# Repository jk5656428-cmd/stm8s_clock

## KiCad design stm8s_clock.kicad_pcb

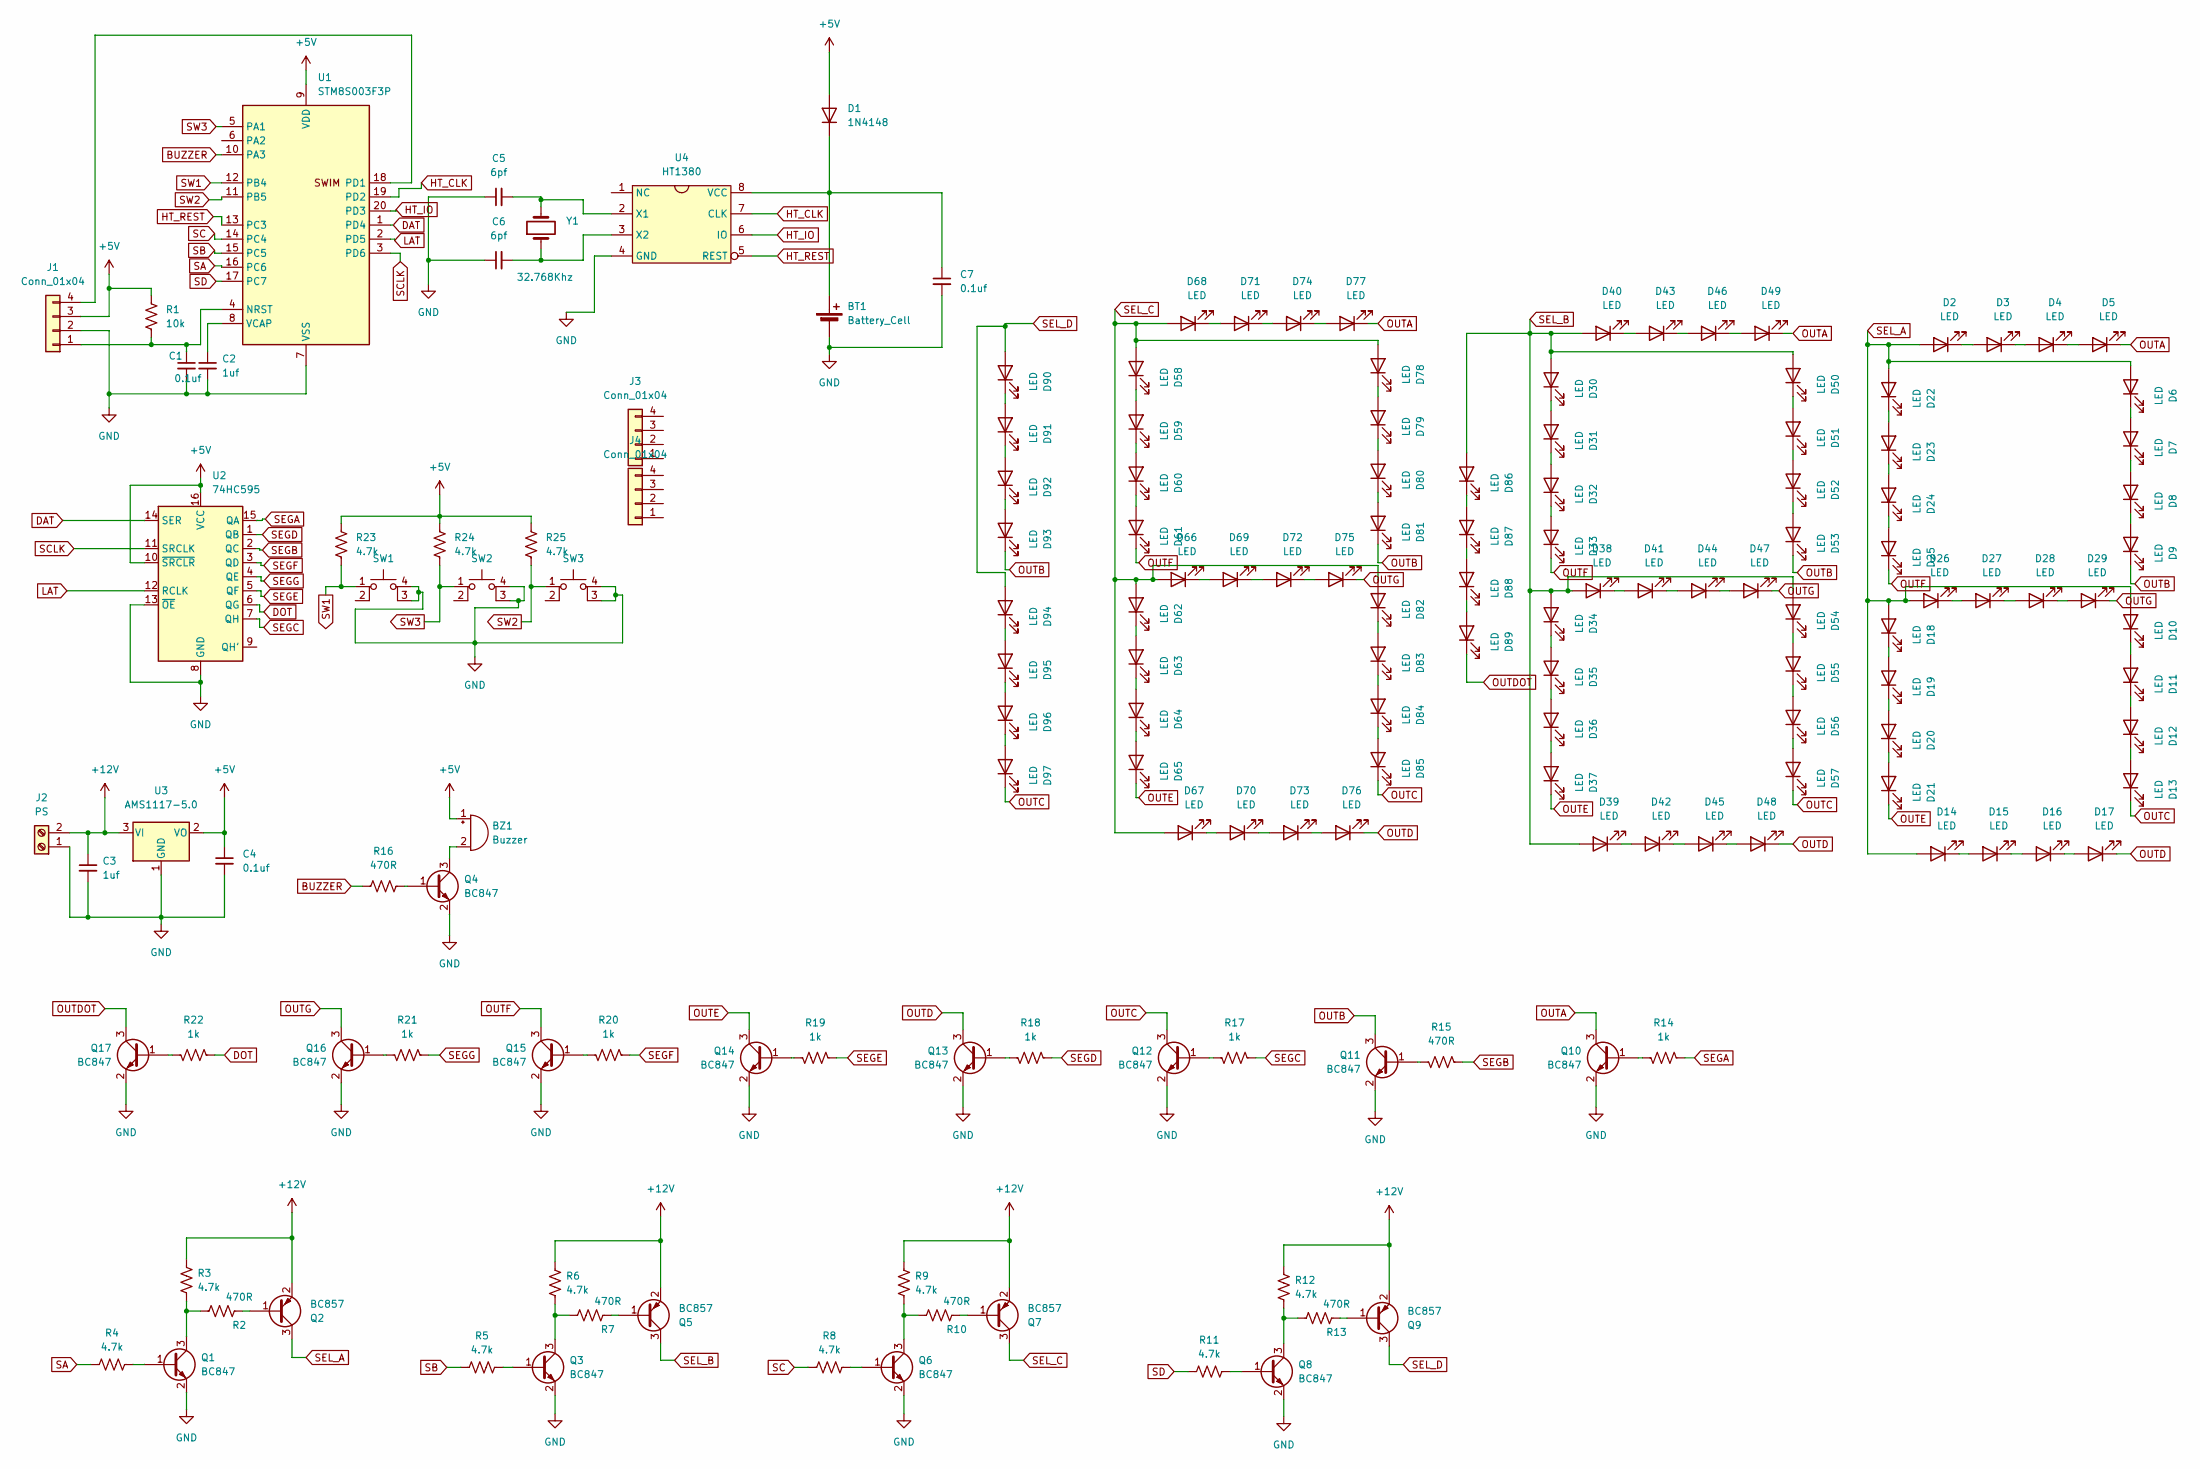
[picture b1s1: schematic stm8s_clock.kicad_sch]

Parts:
BT1: Battery_Cell
BZ1: Buzzer; Buzzer_12x9.5RM7.6
C1: 0.1uf; C_1206_3216Metric_Pad1.33x1.80mm_HandSolder
C2: 1uf; C_0805_2012Metric_Pad1.18x1.45mm_HandSolder
C3: 1uf; C_1206_3216Metric
C4, C7: 0.1uf; C_1206_3216Metric
C5, C6: 6pf; C_Disc_D5.0mm_W2.5mm_P5.00mm
D1: 1N4148; D_DO-35_SOD27_P7.62mm_Horizontal
D2, D3, D4, D5, D6, D7, D8, D9, D10, D11, D12, D13, D14, D15, D16, D17, D18, D19, D20, D21, D22, D23, D24, D25, D26, D27, D28, D29, D30, D31, D32, D33, D34, D35, D36, D37, D38, D39, D40, D41, D42, D43, D44, D45, D46, D47, D48, D49, D50, D51, D52, D53, D54, D55, D56, D57, D58, D59, D60, D61, D62, D63, D64, D65, D66, D67, D68, D69, D70, D71, D72, D73, D74, D75, D76, D77, D78, D79, D80, D81, D82, D83, D84, D85, D86, D87, D88, D89, D90, D91, D92, D93, D94, D95, D96, D97: LED; LED_D5.0mm
J1, J3, J4: Conn_01x04; PinSocket_1x04_P2.54mm_Vertical
J2: PS; TerminalBlock_Phoenix_MKDS-1,5-2_1x02_P5.00mm_Horizontal
Q1, Q3, Q4, Q6, Q8, Q10, Q11, Q12, Q13, Q14, Q15, Q16, Q17: BC847; SOT-23
Q2, Q5, Q7, Q9: BC857; SOT-23
R1: 10k; R_1206_3216Metric_Pad1.30x1.75mm_HandSolder
R2, R7, R10, R13, R15, R16: 470R; R_1206_3216Metric
R3, R4, R5, R6, R8, R9, R11, R12: 4.7k; R_1206_3216Metric
R14, R17, R18, R19, R20, R21, R22: 1k; R_1206_3216Metric
R23, R24, R25: 4.7k; R_1206_3216Metric_Pad1.30x1.75mm_HandSolder
SW1, SW2, SW3: SW_MEC_5E; SW_PUSH_6mm_H13mm
U1: STM8S003F3P; TSSOP-20_4.4x6.5mm_P0.65mm
U2: 74HC595; SOIC-16_3.9x9.9mm_P1.27mm
U3: AMS1117-5.0; SOT-223-3_TabPin2
U4: HT1380; DIP-8_W7.62mm_LongPads
Y1: 32.768Khz; Crystal_AT310_D3.0mm_L10.0mm_Horizontal

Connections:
+5V: BZ1.1 (+), C4.1, D1.2 (A), J1.3, R1.2, R23.1, R24.1, R25.1, U1.9 (VDD), U2.10 (~SRCLR), U2.16 (VCC), U3.2 (VO)
+12V: C3.1, J2.2, Q2.2 (E), Q5.2 (E), Q7.2 (E), Q9.2 (E), R3.2, R6.2, R9.2, R12.2, U3.3 (VI)
BUZZER: R16.1, U1.10 (PA3)
DAT: U1.1 (PD4), U2.14 (SER)
DOT: R22.1, U2.6 (QG)
GND: BT1.2 (-), C1.2, C2.2, C3.2, C4.2, C5.1, C6.1, C7.2, J1.2, J2.1, Q1.2 (E), Q3.2 (E), Q4.2 (E), Q6.2 (E), Q8.2 (E), Q10.2 (E), Q11.2 (E), Q12.2 (E), Q13.2 (E), Q14.2 (E), Q15.2 (E), Q16.2 (E), Q17.2 (E), SW1.3 (K), SW1.4 (A), SW2.3 (K), SW2.4 (A), SW3.3 (K), SW3.4 (A), U1.7 (VSS), U2.8 (GND), U2.13 (~OE), U3.1 (GND), U4.4 (GND)
HT_CLK: U1.19 (PD2), U4.7 (CLK)
HT_IO: U1.20 (PD3), U4.6 (IO)
HT_REST: U1.13 (PC3), U4.5 (REST)
LAT: U1.2 (PD5), U2.12 (RCLK)
unnamed: BT1.1 (+), C7.1, D1.1 (K), U4.8 (VCC)
unnamed: BZ1.2 (-), Q4.3 (C)
unnamed: D2.1 (K), D3.2 (A)
unnamed: D3.1 (K), D4.2 (A)
unnamed: D4.1 (K), D5.2 (A)
unnamed: D6.1 (K), D7.2 (A)
unnamed: D7.1 (K), D8.2 (A)
unnamed: D8.1 (K), D9.2 (A)
unnamed: D10.1 (K), D11.2 (A)
unnamed: D11.1 (K), D12.2 (A)
unnamed: D12.1 (K), D13.2 (A)
unnamed: D14.1 (K), D15.2 (A)
unnamed: D15.1 (K), D16.2 (A)
unnamed: D16.1 (K), D17.2 (A)
unnamed: D18.1 (K), D19.2 (A)
unnamed: D19.1 (K), D20.2 (A)
unnamed: D20.1 (K), D21.2 (A)
unnamed: D22.1 (K), D23.2 (A)
unnamed: D23.1 (K), D24.2 (A)
unnamed: D24.1 (K), D25.2 (A)
unnamed: D26.1 (K), D27.2 (A)
unnamed: D27.1 (K), D28.2 (A)
unnamed: D28.1 (K), D29.2 (A)
unnamed: D30.1 (K), D31.2 (A)
unnamed: D31.1 (K), D32.2 (A)
unnamed: D32.1 (K), D33.2 (A)
unnamed: D34.1 (K), D35.2 (A)
unnamed: D35.1 (K), D36.2 (A)
unnamed: D36.1 (K), D37.2 (A)
unnamed: D38.1 (K), D41.2 (A)
unnamed: D39.1 (K), D42.2 (A)
unnamed: D40.1 (K), D43.2 (A)
unnamed: D41.1 (K), D44.2 (A)
unnamed: D42.1 (K), D45.2 (A)
unnamed: D43.1 (K), D46.2 (A)
unnamed: D44.1 (K), D47.2 (A)
unnamed: D45.1 (K), D48.2 (A)
unnamed: D46.1 (K), D49.2 (A)
unnamed: D50.1 (K), D51.2 (A)
unnamed: D51.1 (K), D52.2 (A)
unnamed: D52.1 (K), D53.2 (A)
unnamed: D54.1 (K), D55.2 (A)
unnamed: D55.1 (K), D56.2 (A)
unnamed: D56.1 (K), D57.2 (A)
unnamed: D58.1 (K), D59.2 (A)
unnamed: D59.1 (K), D60.2 (A)
unnamed: D60.1 (K), D61.2 (A)
unnamed: D62.1 (K), D63.2 (A)
unnamed: D63.1 (K), D64.2 (A)
unnamed: D64.1 (K), D65.2 (A)
unnamed: D66.1 (K), D69.2 (A)
unnamed: D67.1 (K), D70.2 (A)
unnamed: D68.1 (K), D71.2 (A)
unnamed: D69.1 (K), D72.2 (A)
unnamed: D70.1 (K), D73.2 (A)
unnamed: D71.1 (K), D74.2 (A)
unnamed: D72.1 (K), D75.2 (A)
unnamed: D73.1 (K), D76.2 (A)
unnamed: D74.1 (K), D77.2 (A)
unnamed: D78.1 (K), D79.2 (A)
unnamed: D79.1 (K), D80.2 (A)
unnamed: D80.1 (K), D81.2 (A)
unnamed: D82.1 (K), D83.2 (A)
unnamed: D83.1 (K), D84.2 (A)
unnamed: D84.1 (K), D85.2 (A)
unnamed: D86.1 (K), D87.2 (A)
unnamed: D87.1 (K), D88.2 (A)
unnamed: D88.1 (K), D89.2 (A)
unnamed: D90.1 (K), D91.2 (A)
unnamed: D91.1 (K), D92.2 (A)
unnamed: D92.1 (K), D93.2 (A)
unnamed: D94.1 (K), D95.2 (A)
unnamed: D95.1 (K), D96.2 (A)
unnamed: D96.1 (K), D97.2 (A)
unnamed: C1.1, J1.1, R1.1, U1.4 (NRST)
unnamed: J1.4, U1.18 (PD1)
unnamed: Q1.1 (B), R4.1
unnamed: Q1.3 (C), R2.1, R3.1
unnamed: Q2.1 (B), R2.2
unnamed: Q3.1 (B), R5.1
unnamed: Q3.3 (C), R6.1, R7.1
unnamed: Q4.1 (B), R16.2
unnamed: Q5.1 (B), R7.2
unnamed: Q6.1 (B), R8.1
unnamed: Q6.3 (C), R9.1, R10.1
unnamed: Q7.1 (B), R10.2
unnamed: Q8.1 (B), R11.1
unnamed: Q8.3 (C), R12.1, R13.1
unnamed: Q9.1 (B), R13.2
unnamed: Q10.1 (B), R14.2
unnamed: Q11.1 (B), R15.2
unnamed: Q12.1 (B), R17.2
unnamed: Q13.1 (B), R18.2
unnamed: Q14.1 (B), R19.2
unnamed: Q15.1 (B), R20.2
unnamed: Q16.1 (B), R21.2
unnamed: Q17.1 (B), R22.2
unnamed: C2.1, U1.8 (VCAP)
unnamed: C5.2, U4.2 (X1), Y1.2
unnamed: C6.2, U4.3 (X2), Y1.1
OUTA: D5.1 (K), D49.1 (K), D77.1 (K), Q10.3 (C)
OUTB: D9.1 (K), D53.1 (K), D81.1 (K), D93.1 (K), Q11.3 (C)
OUTC: D13.1 (K), D57.1 (K), D85.1 (K), D97.1 (K), Q12.3 (C)
OUTD: D17.1 (K), D48.1 (K), D76.1 (K), Q13.3 (C)
OUTDOT: D89.1 (K), Q17.3 (C)
OUTE: D21.1 (K), D37.1 (K), D65.1 (K), Q14.3 (C)
OUTF: D25.1 (K), D33.1 (K), D61.1 (K), Q15.3 (C)
OUTG: D29.1 (K), D47.1 (K), D75.1 (K), Q16.3 (C)
SA: R4.2, U1.16 (PC6)
SB: R5.2, U1.15 (PC5)
SC: R8.2, U1.14 (PC4)
SCLK: U1.3 (PD6), U2.11 (SRCLK)
SD: R11.2, U1.17 (PC7)
SEGA: R14.1, U2.15 (QA)
SEGB: R15.1, U2.2 (QC)
SEGC: R17.1, U2.7 (QH)
SEGD: R18.1, U2.1 (QB)
SEGE: R19.1, U2.5 (QF)
SEGF: R20.1, U2.3 (QD)
SEGG: R21.1, U2.4 (QE)
SEL_A: D2.2 (A), D6.2 (A), D10.2 (A), D14.2 (A), D18.2 (A), D22.2 (A), D26.2 (A), Q2.3 (C)
SEL_B: D30.2 (A), D34.2 (A), D38.2 (A), D39.2 (A), D40.2 (A), D50.2 (A), D54.2 (A), D86.2 (A), Q5.3 (C)
SEL_C: D58.2 (A), D62.2 (A), D66.2 (A), D67.2 (A), D68.2 (A), D78.2 (A), D82.2 (A), Q7.3 (C)
SEL_D: D90.2 (A), D94.2 (A), Q9.3 (C)
SW1: R23.2, SW1.1, U1.12 (PB4)
SW2: R25.2, SW3.1, U1.11 (PB5)
SW3: R24.2, SW2.1, U1.5 (PA1)

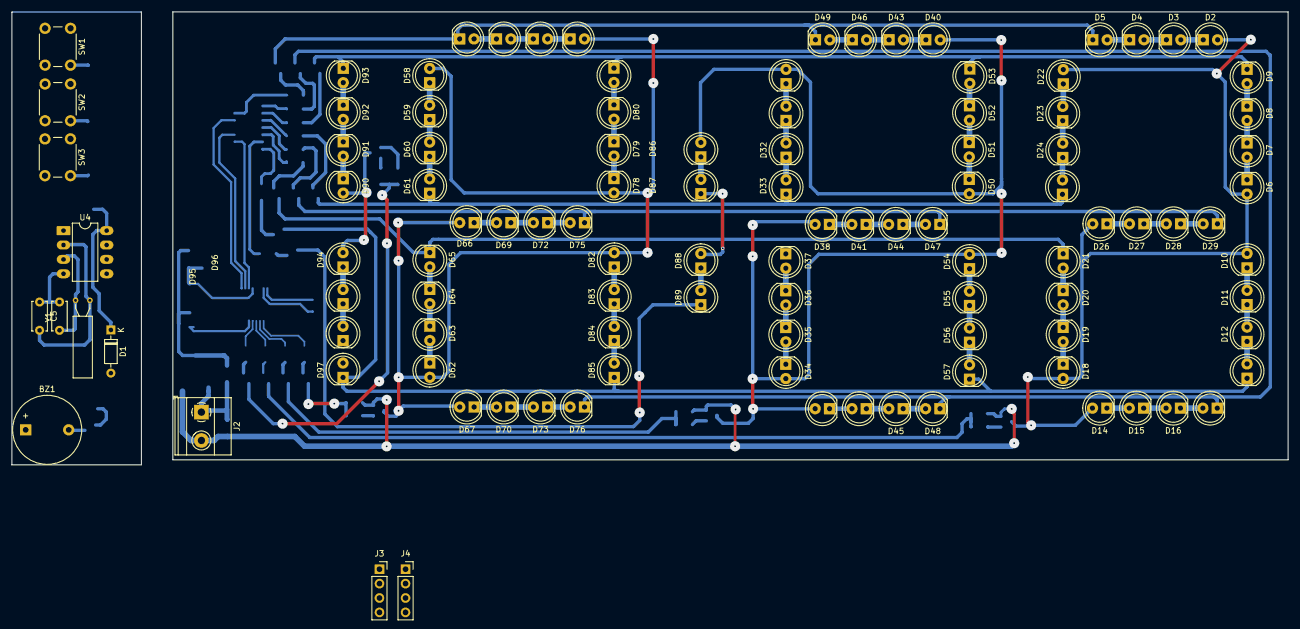
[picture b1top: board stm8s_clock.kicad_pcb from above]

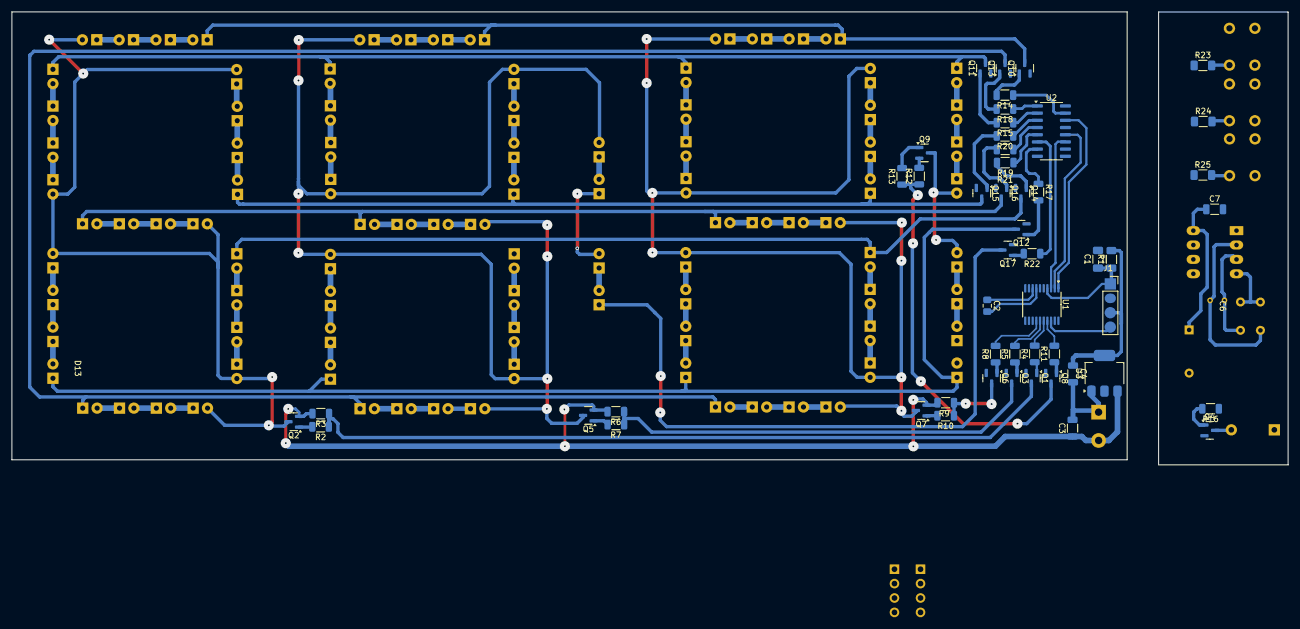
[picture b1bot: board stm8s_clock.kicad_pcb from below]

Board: 2 copper layers, 197.0 x 79.1 mm, 159 parts (51 on the bottom side), 136 nets.

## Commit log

2026-03-27 This is project innitilation
2026-03-27 move transistor to workspace
2026-03-27 component position changes
2026-04-11 connect to all segment and each digit or shift register to connect each other
2026-04-14 add a new pcb creat
